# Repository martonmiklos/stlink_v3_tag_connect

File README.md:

# STLink-v3 SWIM to Tag connect TC2030-MCP adapter board

Replacement board for the MB1440 to expose the SWIM interface to RJ10 for the TAG-connect TC2030-MCP adapter cable.

SWIM level shifter interface is reverse engineered from the MB1440.

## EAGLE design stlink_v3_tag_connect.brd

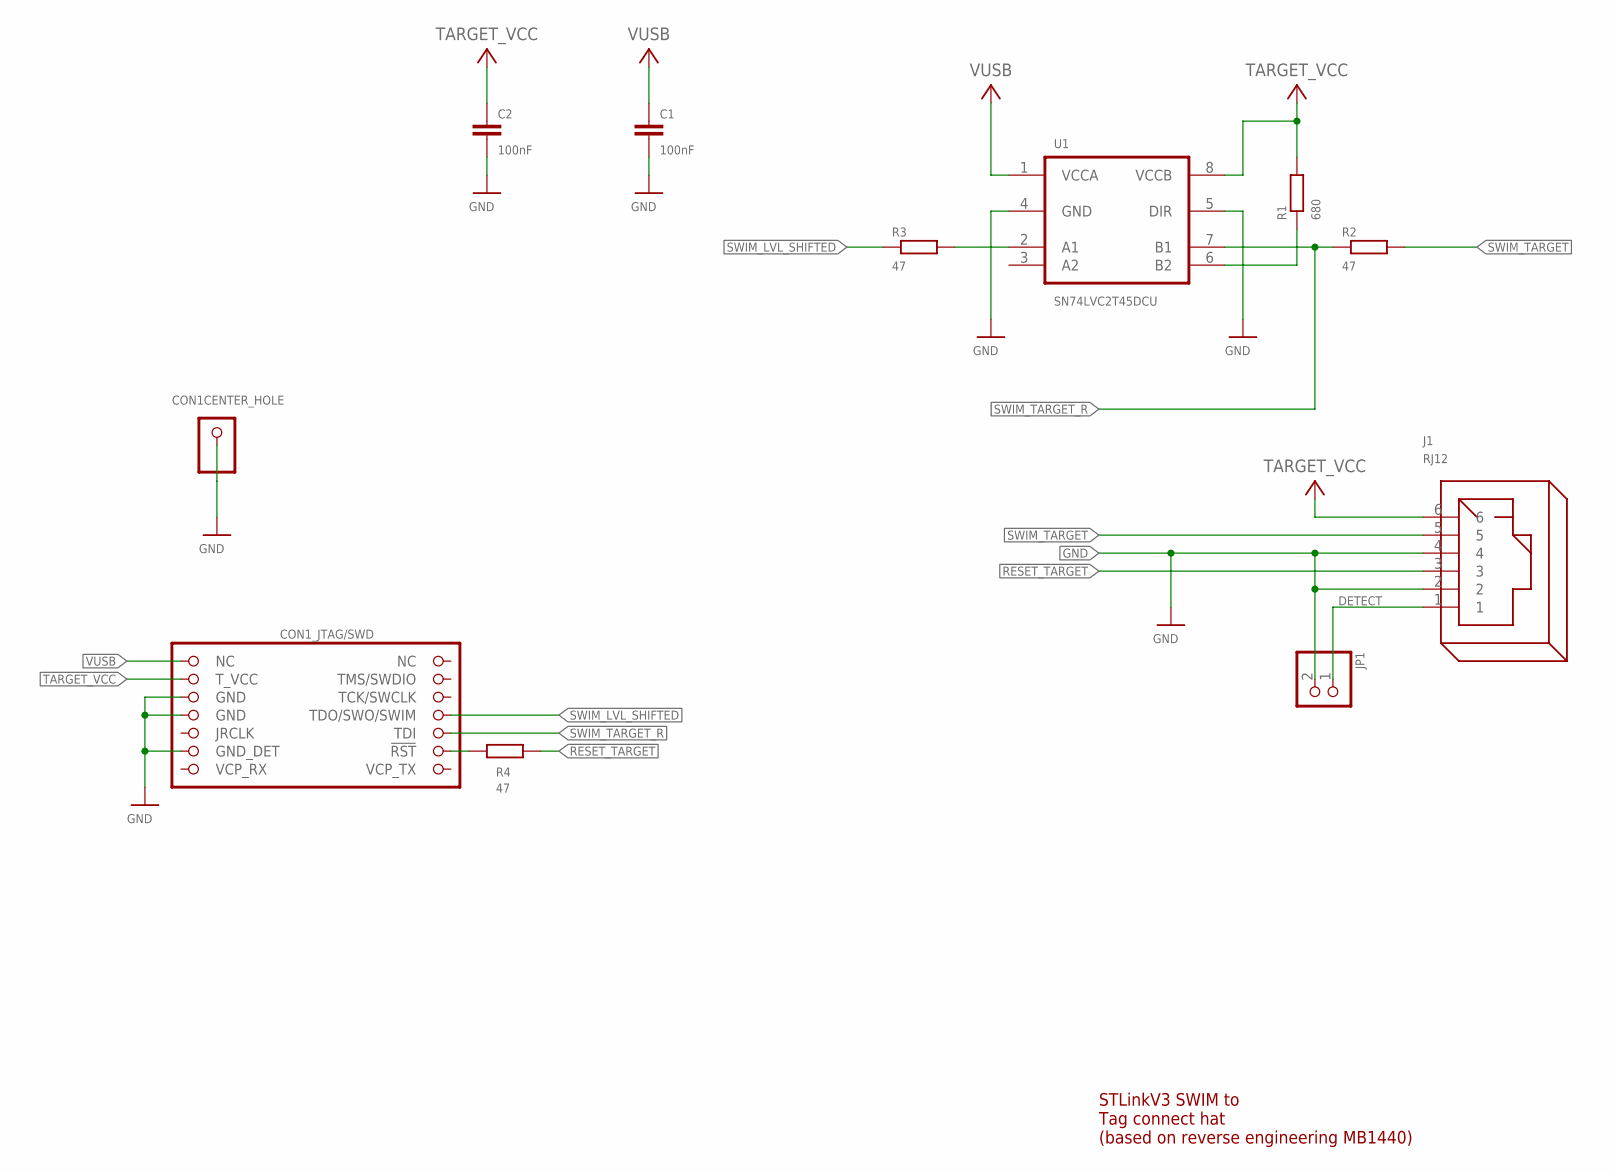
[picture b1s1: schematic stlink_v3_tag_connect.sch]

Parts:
C1, C2: 100nF; C0603
CON1: STLINK_V3_HAT_SWD/JTAG_MINIMAL; STLINKV3_HAT_JTAG_MINIMAL
J1: RJ12
JP1: PINHD-1X2; 1X02
R1: 680; R0603
R2, R3, R4: 47; R0603
U1: SN74LVC2T45DCU; US8-DCU

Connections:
!RESET_STLINK: CON1.STDC_14_12 (!RST), R4.1
!RESET_TARGET: J1.3, R4.2
DETECT: J1.1, JP1.1
GND: C1.2, C2.2, CON1.CENTER (1), CON1.STDC_14_5 (GND), CON1.STDC_14_7 (GND), CON1.STDC_14_11 (GND_DET), J1.2, J1.4, JP1.2, U1.4 (GND), U1.5 (DIR)
unnamed: R1.1, U1.6 (B2)
SWIM_LVL_SHIFTED: CON1.STDC_14_8 (TDO/SWO/SWIM), R3.1
SWIM_LVL_SHIFTED_R: R3.2, U1.2 (A1)
SWIM_TARGET: J1.5, R2.2
SWIM_TARGET_R: CON1.STDC_14_10 (TDI), R2.1, U1.7 (B1)
TARGET_VCC: C2.1, CON1.STDC_14_3 (T_VCC), J1.6, R1.2, U1.8 (VCCB)
VUSB: C1.1, CON1.STDC_14_1 (NC), U1.1 (VCCA)

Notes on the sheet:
STLinkV3 SWIM to Tag connect hat (based on reverse engineering MB1440)

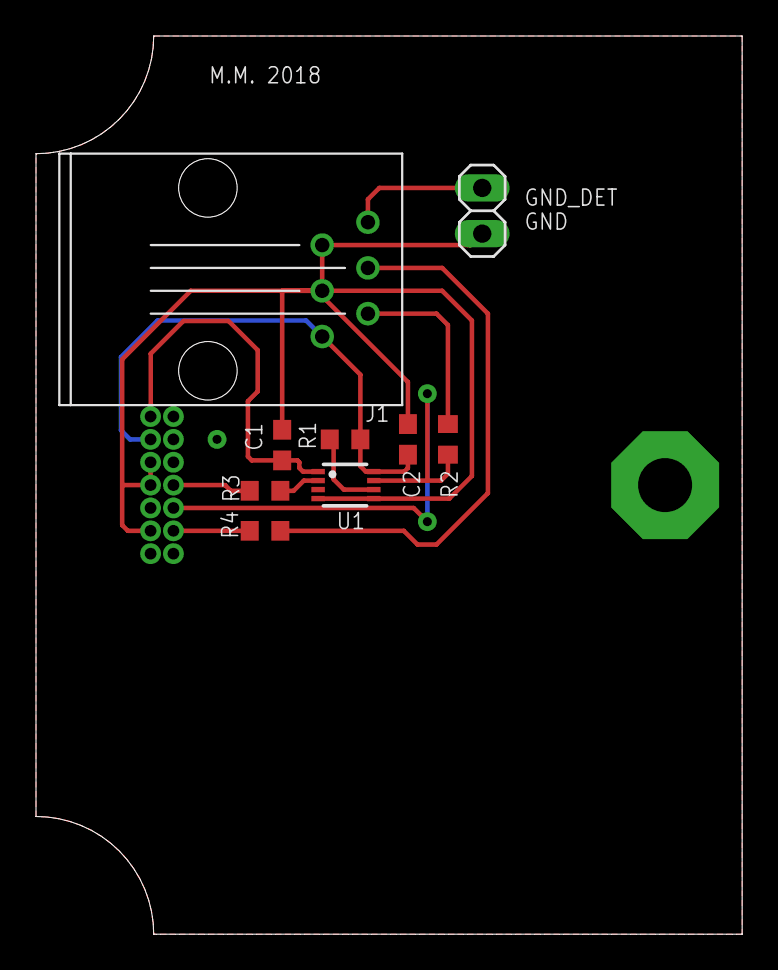
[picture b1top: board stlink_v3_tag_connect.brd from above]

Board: 2 copper layers, 39.2 x 49.9 mm, 10 parts (0 on the bottom side), 11 nets.

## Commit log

2018-11-03 Initial add
2018-11-12 Added SWD popoption
2018-11-12 Routing done
2018-11-12 Fix missing SWIM data line back to the StLink
2019-02-21 - Added mgt MCU - Moved RJ12 to the middle - Fixed SWD pinout
2019-07-25 Align LEDs
2019-09-06 Added SCH in PNG
2019-09-06 Sch prettify

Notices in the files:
parts and their libraries:
74LV: Copyright (C) 2008, Bob Starr
